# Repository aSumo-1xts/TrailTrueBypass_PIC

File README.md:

<h1 align="center">
TrailTrueBypass_PIC
</h1>

<div align="center">

**A project for a trail-bypass with an DIP8 PIC microcontroller.**

</div>

## Features

- Normal true bypass when Trail mode off
- Selectable operating mode: Alternate or Momentary
- Set the power-on state: ON or OFF
- (Option) Selectable timing to switch: when-pressed or when-released
- Automatically bypasses if power is accidentally turned off

## Verified on

- PIC12F629
- PIC12F675

## dir: KiCad

KiCad関連のファイル一式です。

ガーバーファイルは[Release](https://github.com/asumo-1xts/TrailTrueBypass_PIC/releases)からダウンロードできます。

## dir: src

PICマイコン用のソースコード群です。

プロジェクト管理の様式はVScode用のMPLAB Extension Packに準拠しています。

コンパイル後のhexファイルは[Release](https://github.com/asumo-1xts/TrailTrueBypass_PIC/releases)からダウンロードできます。

PICマイコン間で共通のソースコードはsrc直下に、そうでないものはそのハードウェアの名前の付いたディレクトリに入っています。

src/header.hの冒頭で所望のPICマイコンのヘッダーファイルをincludeするだけで、そのPICマイコンが書き込み対象となります。

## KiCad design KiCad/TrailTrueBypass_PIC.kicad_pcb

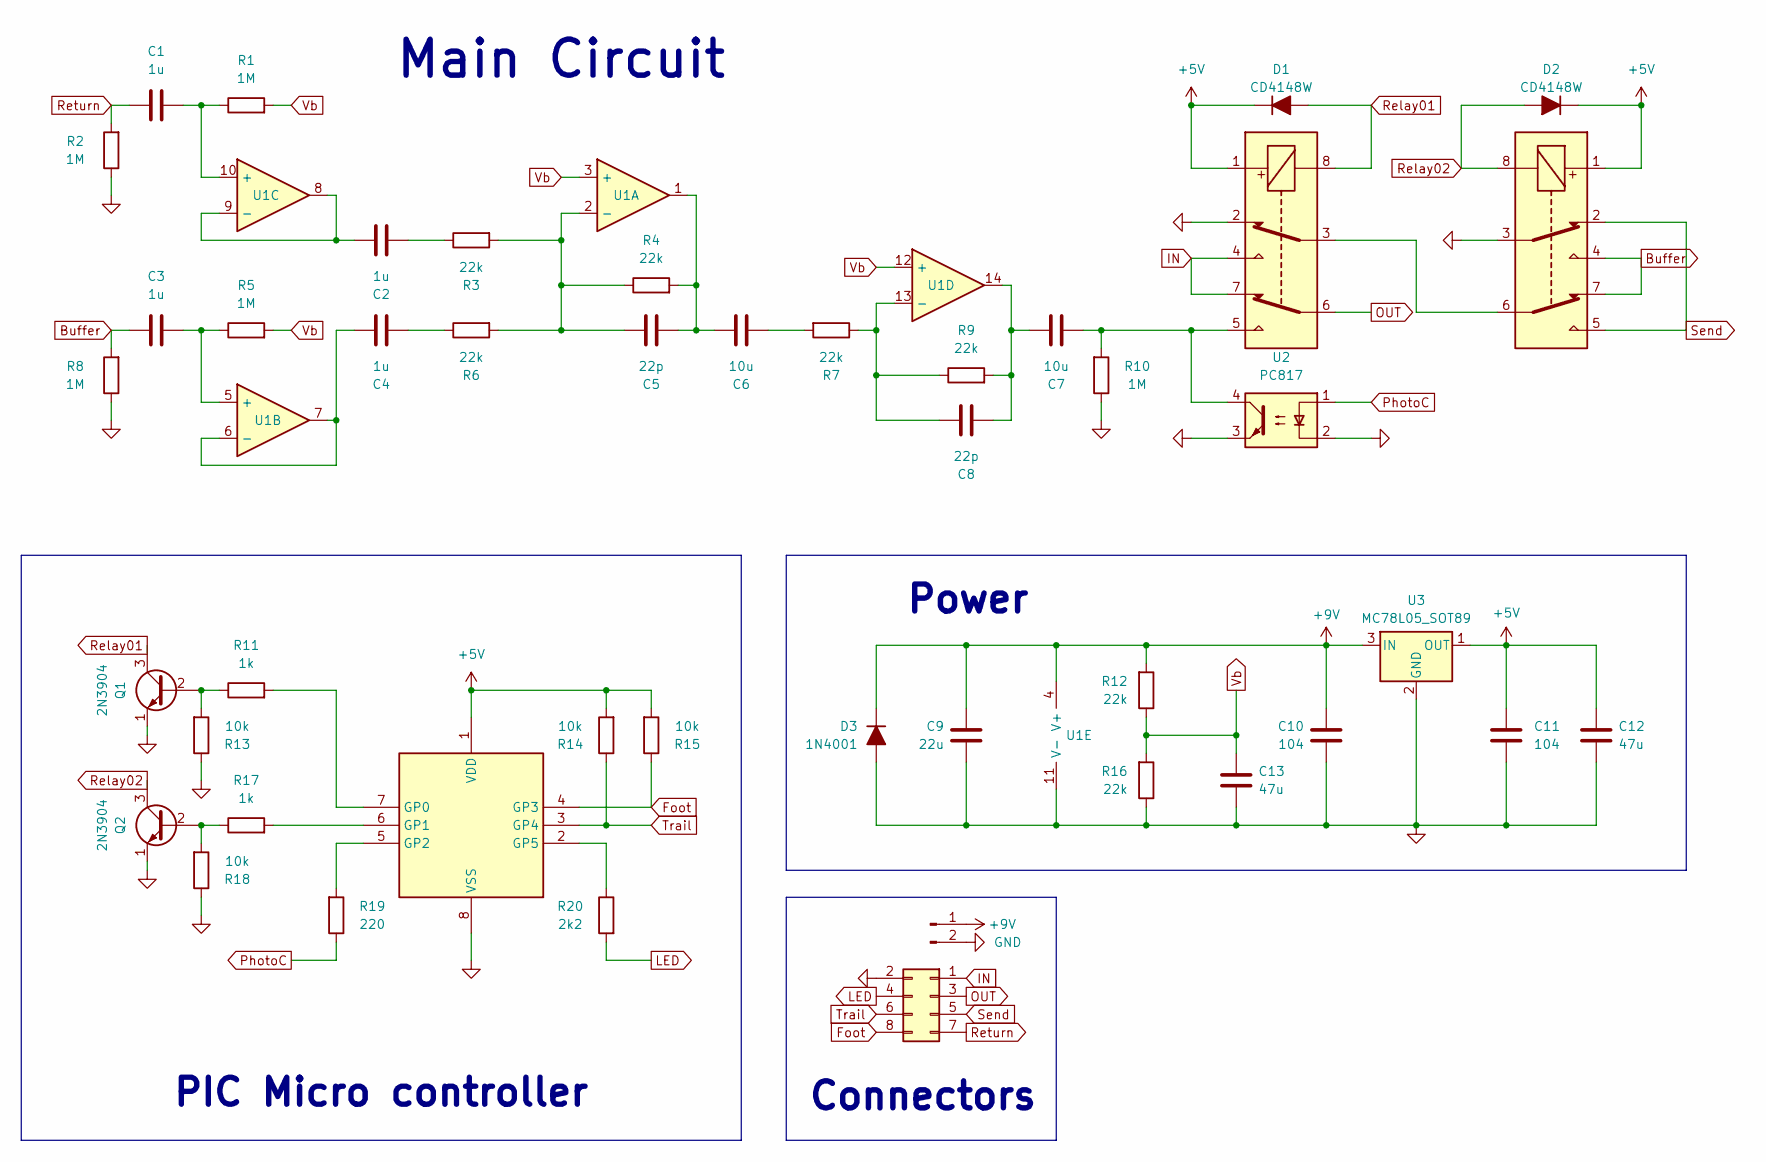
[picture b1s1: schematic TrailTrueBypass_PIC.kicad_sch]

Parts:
C1, C2, C3, C4: 1u; C_1206_3216Metric_Pad1.33x1.80mm_HandSolder
C5, C8: 22p; C_0402_1005Metric
C6, C7: 10u; C_1812_4532Metric_Pad1.57x3.40mm_HandSolder
C9: 22u; C_0805_2012Metric
C10, C11: 104; C_0402_1005Metric
C12: 47u; C_1206_3216Metric
C13: 47u; C_1812_4532Metric_Pad1.57x3.40mm_HandSolder
D1, D2: CD4148W; D_SOD-323
D3: 1N4001; D_SOD-123
J1: Conn_01x05_Pin; PinHeader_1x02_P2.54mm_Vertical
J2: Conn_02x04_Top_Bottom; PinHeader_2x04_P2.54mm_Vertical
K1, K2: G6S-2; Relay_DPDT_Omron_G6K-2F-Y
Q1, Q2: 2N3904; MMBT3904
R1, R2, R5, R8, R10: 1M; R_0603_1608Metric
R3, R4, R6, R7, R9: 22k; R_0603_1608Metric
R11, R17: 1k; R_0603_1608Metric
R12, R16: 22k; R_0805_2012Metric
R13, R14, R15, R18: 10k; R_0603_1608Metric
R19: 220; R_0603_1608Metric
R20: 2k2; R_0603_1608Metric
U1: Opamp_Quad; SOIC-14_3.9x8.7mm_P1.27mm
U2: PC817; DIP-4_W7.62mm
U3: MC78L05_SOT89; SOT-89-3
U4: PIC12F675-xP; DIP-8_W7.62mm_Socket

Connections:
+5V: C11.1, C12.1, D1.1 (K), D2.1 (K), K1.1, K2.1, R14.2, R15.2, U3.1 (OUT), U4.1 (VDD)
+9V: C9.1, C10.1, D3.1 (K), J1.1, R12.2, U1.4 (V+), U3.3 (IN)
Buffer: C3.1, K2.4, K2.7, R8.2
Foot: J2.8, R15.1, U4.4 (GP3)
GND: C9.2, C10.2, C11.2, C12.2, C13.2, D3.2 (A), J1.2, J2.2, K1.2, K2.3, Q1.1 (E), Q2.1 (E), R2.1, R8.1, R10.1, R13.1, R16.1, R18.1, U1.11 (V-), U2.2, U2.3, U3.2 (GND), U4.8 (VSS)
IN: J2.1, K1.4, K1.7
LED: J2.4, R20.2
unnamed: C2.2, R3.1
unnamed: C4.2, R6.1
unnamed: C5.2, C6.1, R4.2, U1.1
unnamed: C6.2, R7.2
unnamed: C7.1, K1.5, R10.2, U2.4
unnamed: C7.2, C8.2, R9.2, U1.14
unnamed: K1.3, K2.6
unnamed: Q1.2 (B), R11.1, R13.2
unnamed: Q2.2 (B), R17.1, R18.2
unnamed: C5.1, R3.2, R4.1, R6.2, U1.2 (-)
unnamed: C3.2, R5.1, U1.5 (+)
unnamed: C4.1, U1.6 (-), U1.7
unnamed: C1.2, R1.1, U1.10 (+)
unnamed: C2.1, U1.8, U1.9 (-)
unnamed: C8.1, R7.1, R9.1, U1.13 (-)
unnamed: R11.2, U4.7 (GP0)
unnamed: R17.2, U4.6 (GP1)
unnamed: R19.2, U4.5 (GP2)
unnamed: R20.1, U4.2 (GP5)
OUT: J2.3, K1.6
PhotoC: R19.1, U2.1
Relay01: D1.2 (A), K1.8, Q1.3 (C)
Relay02: D2.2 (A), K2.8, Q2.3 (C)
Return: C1.1, J2.7, R2.2
Send: J2.5, K2.2, K2.5
Trail: J2.6, R14.1, U4.3 (GP4)
Vb: C13.1, R1.2, R5.2, R12.1, R16.2, U1.3 (+), U1.12 (+)

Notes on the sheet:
Main Circuit
Connectors
Power
PIC Micro controller

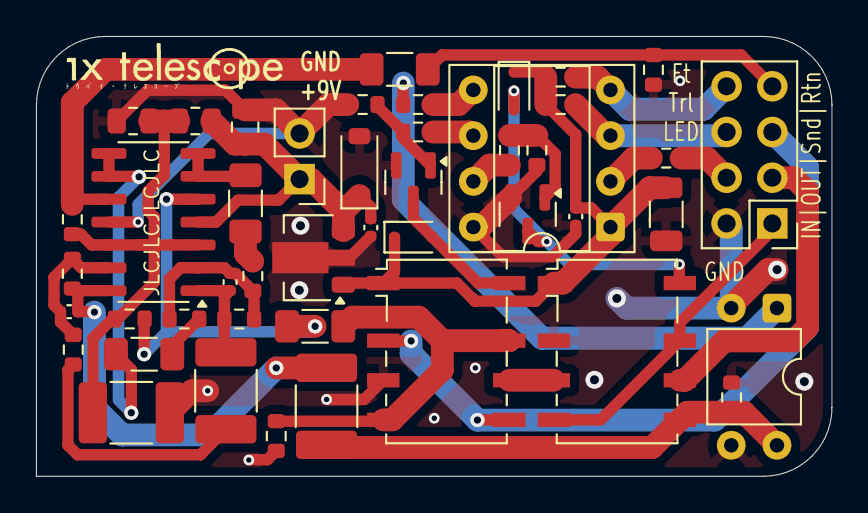
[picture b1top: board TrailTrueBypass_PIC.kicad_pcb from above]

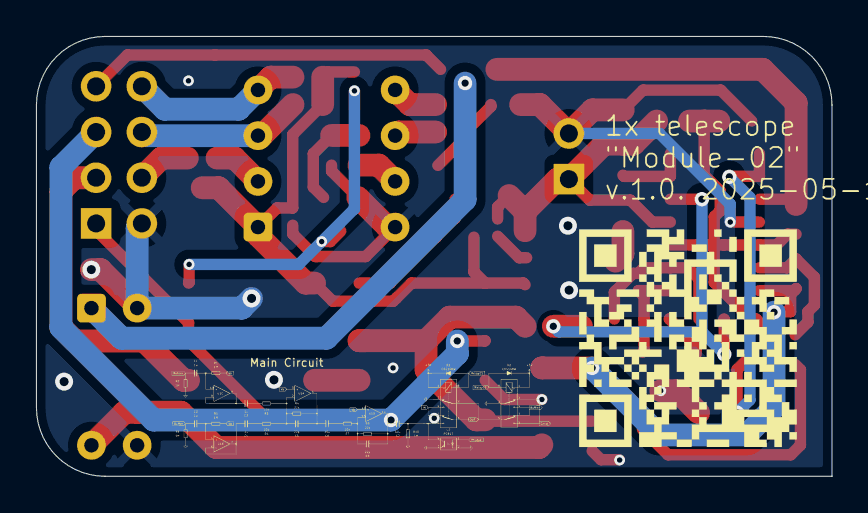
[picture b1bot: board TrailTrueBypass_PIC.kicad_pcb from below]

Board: 2 copper layers, 44.2 x 24.4 mm, 49 parts (2 on the bottom side), 34 nets.

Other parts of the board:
G1, G2, G3: LOGO

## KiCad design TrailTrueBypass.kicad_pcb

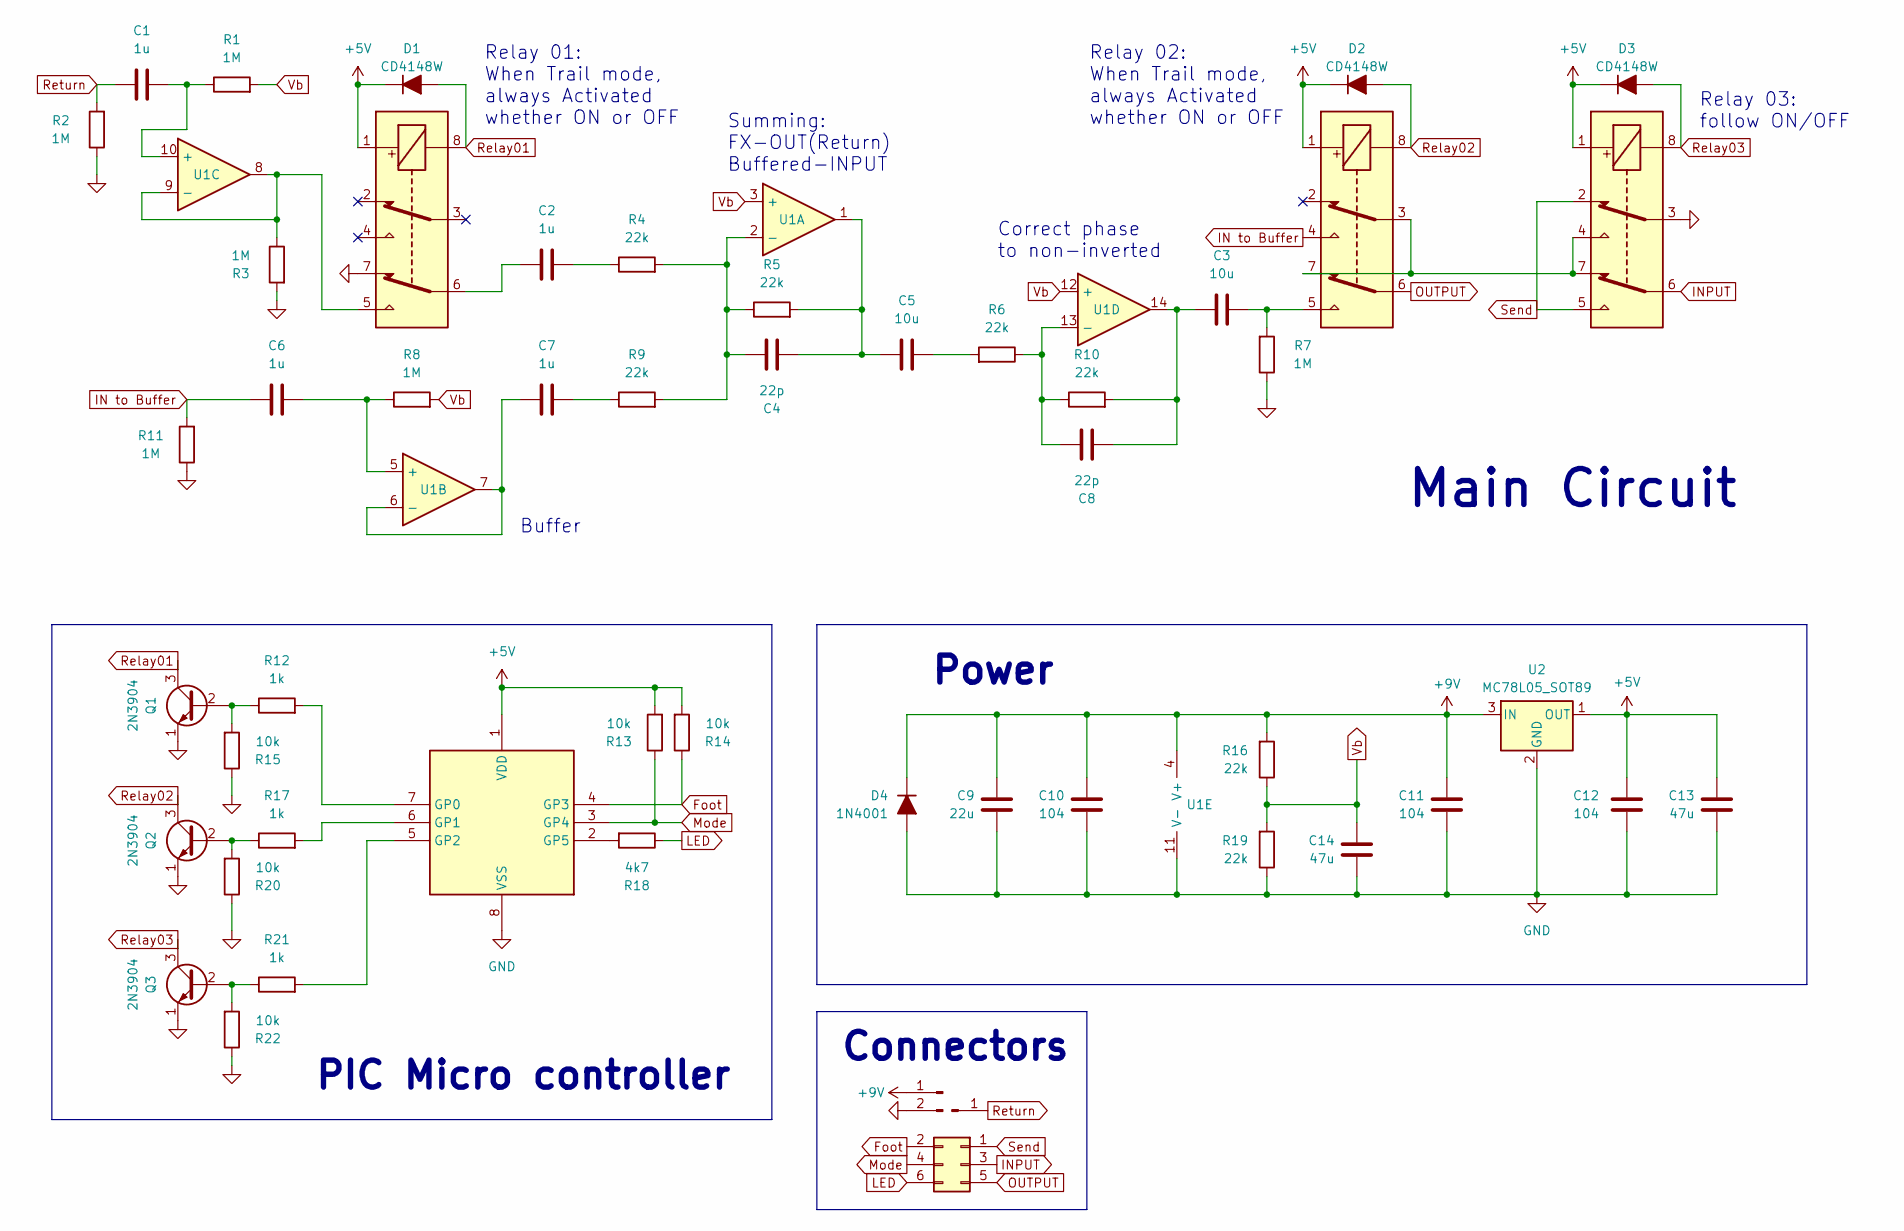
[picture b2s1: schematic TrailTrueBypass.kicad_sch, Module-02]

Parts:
C1, C2, C6, C7: 1u; C_1206_3216Metric_Pad1.33x1.80mm_HandSolder
C3, C5: 10u; C_1812_4532Metric_Pad1.57x3.40mm_HandSolder
C4, C8: 22p; C_0402_1005Metric
C9: 22u; C_0805_2012Metric
C10, C11, C12: 104; C_0402_1005Metric
C13: 47u; C_1206_3216Metric
C14: 47u; C_1812_4532Metric_Pad1.57x3.40mm_HandSolder
D1, D2, D3: CD4148W; D_SOD-323
D4: 1N4001; D_SOD-123
J1: Conn_01x05_Pin; PinHeader_1x02_P2.54mm_Vertical
J2: Conn_01x05_Pin; PinHeader_1x01_P2.54mm_Vertical
J3: Conn_02x03_Top_Bottom; PinHeader_2x03_P2.54mm_Vertical
K1, K2, K3: G6S-2; Relay_DPDT_Omron_G6K-2F-Y
Q1, Q2, Q3: 2N3904; SOT-23
R1, R2, R3, R7, R8, R11: 1M; R_0603_1608Metric
R4, R5, R6, R9, R10: 22k; R_0603_1608Metric
R12, R17, R21: 1k; R_0603_1608Metric
R13, R14, R15, R20, R22: 10k; R_0603_1608Metric
R16, R19: 22k; R_0805_2012Metric
R18: 4k7; R_0603_1608Metric
U1: Opamp_Quad; SOIC-14_3.9x8.7mm_P1.27mm
U2: MC78L05_SOT89; SOT-89-3
U3: PIC12F675-xP; DIP-8_W7.62mm_Socket

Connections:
+5V: C12.1, C13.1, D1.1 (K), D2.1 (K), D3.1 (K), K1.1, K2.1, K3.1, R13.2, R14.2, U2.1 (OUT), U3.1 (VDD)
+9V: C9.1, C10.1, C11.1, D4.1 (K), J1.1, R16.2, U1.4 (V+), U2.3 (IN)
Foot: J3.2, R14.1, U3.4 (GP3)
GND: C9.2, C10.2, C11.2, C12.2, C13.2, C14.2, D4.2 (A), J1.2, K1.7, K3.3, Q1.1 (E), Q2.1 (E), Q3.1 (E), R2.1, R3.2, R7.1, R11.1, R15.1, R19.1, R20.1, R22.1, U1.11 (V-), U2.2 (GND), U3.8 (VSS)
IN to Buffer: C6.1, K2.4, R11.2
INPUT: J3.3, K3.6
LED: J3.6, R18.1
Mode: J3.4, R13.1, U3.3 (GP4)
unnamed: C2.1, K1.6
unnamed: C2.2, R4.1
unnamed: C3.1, K2.5, R7.2
unnamed: C3.2, C8.2, R10.2, U1.14
unnamed: C4.2, C5.1, R5.2, U1.1
unnamed: C5.2, R6.2
unnamed: C7.2, R9.1
unnamed: K2.3, K2.7, K3.4, K3.7
unnamed: Q1.2 (B), R12.1, R15.2
unnamed: Q2.2 (B), R17.1, R20.2
unnamed: Q3.2 (B), R21.1, R22.2
unnamed: C4.1, R4.2, R5.1, R9.2, U1.2 (-)
unnamed: C6.2, R8.1, U1.5 (+)
unnamed: C7.1, U1.6 (-), U1.7
unnamed: C1.2, R1.1, U1.10 (+)
unnamed: K1.5, R3.1, U1.8, U1.9 (-)
unnamed: C8.1, R6.1, R10.1, U1.13 (-)
unnamed: R12.2, U3.7 (GP0)
unnamed: R17.2, U3.6 (GP1)
unnamed: R21.2, U3.5 (GP2)
unnamed: R18.2, U3.2 (GP5)
OUTPUT: J3.5, K2.6
Relay01: D1.2 (A), K1.8, Q1.3 (C)
Relay02: D2.2 (A), K2.8, Q2.3 (C)
Relay03: D3.2 (A), K3.8, Q3.3 (C)
Return: C1.1, J2.1, R2.2
Send: J3.1, K3.2, K3.5
Vb: C14.1, R1.2, R8.2, R16.1, R19.2, U1.3 (+), U1.12 (+)

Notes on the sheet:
Power
Relay 01: When Trail mode, always Activated whether ON or OFF
Relay 03: follow ON/OFF
Buffer
Relay 02: When Trail mode, always Activated whether ON or OFF
Summing: FX-OUT(Return) Buffered-INPUT
Main Circuit
Correct phase to non-inverted
PIC Micro controller
Connectors

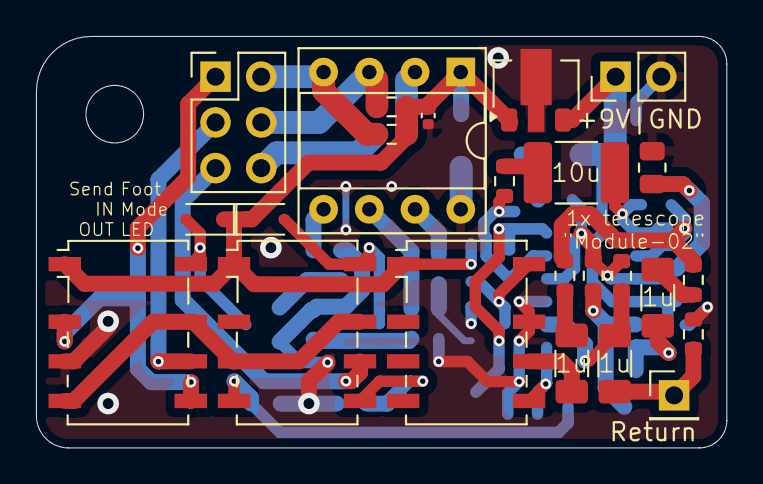
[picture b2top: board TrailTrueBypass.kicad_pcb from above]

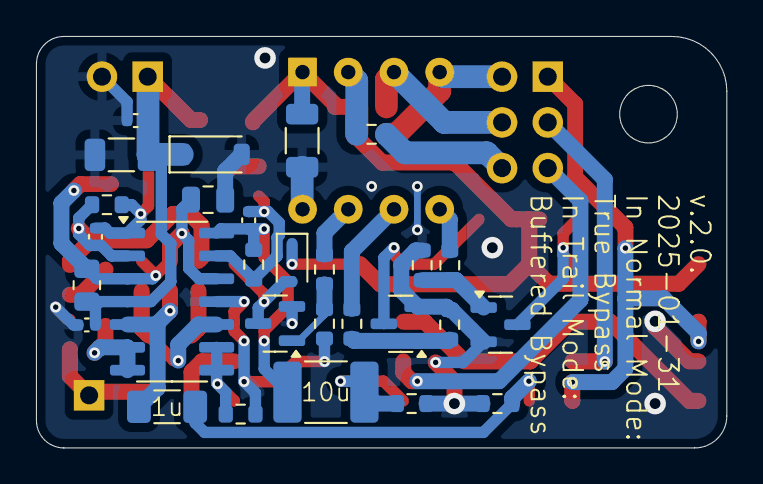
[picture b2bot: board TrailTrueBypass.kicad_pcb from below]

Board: 2 copper layers, 38.4 x 22.9 mm, 53 parts (28 on the bottom side), 36 nets.

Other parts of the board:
H1: MountingHole_3.2mm_M3

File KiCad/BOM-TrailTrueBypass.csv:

Comment,Designator,Footprint,LCSC
Opamp_Quad,U1,SOIC-14_3.9x8.7mm_P1.27mm,C107644
22p,"C4,C8",C_0402_1005Metric,C1555
22k,R19,R_0805_2012Metric,C17560
2N3904,"Q1,Q2,Q3",SOT-23,C20526
1k,"R12,R17,R21",R_0603_1608Metric,C21190
CD4148W,"D1,D2,D3",D_SOD-323,C2128
1M,"R1,R11,R2,R3,R7,R8",R_0603_1608Metric,C22935
4k7,R18,R_0603_1608Metric,C23162
10k,"R13,R14,R15,R20,R22",R_0603_1608Metric,C25804
104,"C10,C11,C12",C_0402_1005Metric,C307331
22k,"R10,R16,R4,R5,R6,R9",R_0603_1608Metric,C31850
22u,C14,C_0805_2012Metric,C45783
G6S-2,"K1,K2,K3",Relay_DPDT_Omron_G6K-2F-Y,C47190
1N4001,D4,D_SOD-123,C64898
MC78L05_SOT89,U2,SOT-89-3,C71136
47u,"C13,C9",C_1206_3216Metric,C96123
PIC12F675-xP,U3,DIP-8_W7.62mm_Socket,
Conn_01x05_Pin,J2,PinHeader_1x01_P2.54mm_Vertical,
Conn_02x03_Top_Bottom,J3,PinHeader_2x03_P2.54mm_Vertical,
10u,C5,C_1812_4532Metric_Pad1.57x3.40mm_HandSolder,
Conn_01x05_Pin,J1,PinHeader_1x02_P2.54mm_Vertical,
1u,C7,C_1206_3216Metric_Pad1.33x1.80mm_HandSolder,
1u,C1,C_1206_3216Metric_Pad1.33x1.80mm_HandSolder,
1u,C6,C_1206_3216Metric_Pad1.33x1.80mm_HandSolder,
10u,C3,C_1812_4532Metric_Pad1.57x3.40mm_HandSolder,
1u,C2,C_1206_3216Metric_Pad1.33x1.80mm_HandSolder,
MountingHole_3.2mm_M3,H1,MountingHole_3.2mm_M3,

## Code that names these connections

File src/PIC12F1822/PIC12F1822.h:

#ifndef PIC12F6XX_H
#define PIC12F6XX_H

#include <stdbool.h>
#include <stdint.h>
#include <xc.h>

#define _XTAL_FREQ 16000000  //!< クロック周波数        16 MHz

#pragma config FOSC = INTOSC  // 内部クロック          使用
#pragma config WDTE = OFF     // Watch-Dogタイマー     不使用
#pragma config PWRTE = ON     // パワーアップタイマー  使用
#pragma config MCLRE = OFF    // リセットピン          不使用
#pragma config BOREN = ON     // Brown-Out検出         使用
#pragma config CP = ON        // プログラム保護        使用
#pragma config CPD = ON       // データ保護            使用

// ピンアウト
#define Relay01 LATAbits.LATA0    //!< Relayピンその1
#define Relay02 LATAbits.LATA1    //!< Relayピンその2
#define Relay03 LATAbits.LATA2    //!< Relayピンその3
#define FootSwitch PORTAbits.RA3  //!< FootSwitchピン（Momentary）
#define ModeSwitch PORTAbits.RA4  //!< ModeSwitchピン（Alternate）
#define LED LATAbits.LATA5        //!< LEDピン

// EEPROMから読み込むグローバル変数
extern bool initState;  // ペダルの初期状態
extern bool momentary;  // モーメンタリ動作の是非
extern bool timing;     // オルタネイト動作時、いつ反転するか

// 関数のプロトタイプ宣言
uint8_t eepRead(uint8_t adress);
void eepWrite(uint8_t adress, uint8_t myData);
void init(void);

#endif /* PIC12F6XX_H */

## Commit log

2025-04-09 add: KiCad上のファイル3種を追加
2025-04-09 update: schファイルの軽微な修正
2025-04-09 update: MITライセンスのバッジを追加
2025-04-09 update: pcbファイルを修正
2025-04-09 move: KiCad用のフォルダを用意
2025-04-09 add: 製造用のcsvファイルを追加
2025-04-09 rename: KiCad用フォルダの名前を変更
2025-04-09 update: KiCadのバッジを追加
2025-04-12 update: READMEに各種バッジを追加
2025-05-09 update: READMEのバッジを編集
2025-05-09 add: MPLABプロジェクトを作成
2025-05-09 add: ソースファイルを追加
2025-05-09 Deploying to doxygen from @ aSumo-1xts/TrailTrueBypass_PIC@1b689f9e2e71fc29a554750bd0725686e5b5eaac 🚀
2025-05-09 Initial doxygen commit
2025-05-09 add: Doxygenを導入
2025-05-09 add: KiBotを導入
2025-05-09 update: READMEを編集
2025-05-09 add: 書き込み用スクリプトを追加
2025-05-09 update: 変数名を変更
2025-05-09 update: 割り込みの可否にマクロを使用
2025-05-09 update: KiBotによる出力先の名前を変更
2025-05-10 update: workflowsの発動条件を編集
2025-05-12 Deploying to doxygen from @ aSumo-1xts/TrailTrueBypass_PIC@3d07d5dd518ae9ca2149bb44c7bfd35b22ef6e28 🚀
2025-05-12 Deploying to doxygen from @ aSumo-1xts/TrailTrueBypass_PIC@1d11a0954b8200d8d1bdb5721f05385bdbdbfa02 🚀
2025-05-12 Deploying to doxygen from @ aSumo-1xts/TrailTrueBypass_PIC@c6bdf3b3916edd1ecaa341c681df5bc6e298f0f6 🚀
2025-05-12 Deploying to doxygen from @ aSumo-1xts/TrailTrueBypass_PIC@8ab9ae5fa12be2d6630d796466b00e16506bb67b 🚀
2025-05-12 update: ハードウェア抽象化を実施
2025-05-12 add: PIC12F1822を追加
2025-05-12 add: PIC16F15313を追加
2025-06-07 update: ポップノイズを逃がす処理を追加
2025-06-07 update: ポップノイズを逃がす処理を追加 (#1)
2025-06-07 Deploying to doxygen from @ aSumo-1xts/TrailTrueBypass_PIC@93d2c6ca58383006b04a49bd9f8c15d569881eb4 🚀
2025-06-07 test: KiBotを起こすためだけのコミット
2025-06-07 test: KiBotを起こすためだけのコミット (#2)
2025-06-07 fix: ローカル記法を削除
2025-06-07 fix: ローカル記法を削除 (#3)
2025-06-07 Deploying to doxygen from @ aSumo-1xts/TrailTrueBypass_PIC@bb2adceda0effd5dcd213590aaeb51eda66c5315 🚀
2025-08-14 update: .gitignoreを調整
2025-08-14 develop: 細かなアップデート (#5)
    * update: .gitignoreを調整
    * update: READMEを編集
2025-08-14 delete: 不要なバックアップファイルを削除
2025-10-20 Deploying to doxygen from @ aSumo-1xts/TrailTrueBypass_PIC@366557323ee8cdc955c6f6e3465d154051a12075 🚀
2025-11-24 feat: clang-formatを導入
2025-11-24 feat: CI/CDにclang-formatを導入 (#2)
2025-11-24 auto: Format code
2025-11-24 Deploying to doxygen from @ asumo-1xts/TrailTrueBypass_PIC@4bdf6e692dff1cffcf5ed157c658eeeba0f9c03d 🚀
2025-11-24 docs: READMEを編集
2025-11-24 docs: READMEを編集 (#3)
2025-11-24 move: READMEをルートから移動
2025-11-24 update: mplab.jsonファイルを更新
2025-11-24 dev: ファイルの移動と更新 (#4)
    * move: READMEをルートから移動
    * update: mplab.jsonファイルを更新
2025-11-24 fix: リンクの誤りを修正
2025-11-24 fix: リンクの誤りを修正 (#5)
2025-12-10 move: .clang-formatを移動
2025-12-10 move: .clang-formatを移動 (#7)
2025-12-10 update: zsh-autoenvを導入
2025-12-12 move: .clang-formatをルートへ再移動
2025-12-12 update: 拡張機能に関する整備
2025-12-12 dev: 開発環境の整備 (#9)
    * move: .clang-formatをルートへ再移動
    * update: 拡張機能に関する整備
2026-01-11 Deploying to doxygen from @ asumo-1xts/TrailTrueBypass_PIC@7947cf924ca1c436cc5774ba6fd627af5bc5f079 🚀
2026-01-11 chore: Update and merge Actions
2026-01-11 docs: Update Doxygen documentation
2026-01-11 chore: Add deploy Action
2026-01-11 chore: Update Clang-Format details
2026-01-11 chore: Add mise tasks
2026-01-15 chore: Update VScode settings
2026-01-16 chore: Merge three Actions
2026-01-21 docs: Delete all
2026-01-21 chore: Undeploy `docs/` and Simplify Action
2026-01-21 feat: Add `.ps1` script to write `*.hex`
2026-01-21 docs: Edit README
2026-01-21 chore: Move doxygen-css from root
